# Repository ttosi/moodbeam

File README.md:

# moodbeam
Arduino, ESP8266 ESP-01 and NeoPixel light bar. Uses a pair of neopixels mounted on each end of an acrylic rod to create a beam of color. ~~The lights are controlled by a RESTful'ish API.~~

The original idea came from the fact that I needed a way to alert people when I was coding "in the zone" so I would, hopefully, be left alone. My plan was to just mount a couple of LEDs behind my LCD that would illuminate the wall red with a button click. The LEDs weren't bright enough to see during the day. Shining them through an acrylic rod with scores in it made the light more visible in bright conditions. The project grew into using different colors to indicate various moods I was in. Buttons became cumbersome so I added an ESP8266 and a mobile app that allows me to choose any color.

## Overall Architecture

### Moodbeam Controller
__Initial Configuration for moodbeam controller__ (`config.lua` does not exist on the ESP8266's flash):
* Configures itself in AP mode
* User connects to the MOODBEAM AP and browses to 192.168.4.1
* The ESP module returns a webpage where an SSID and password of the home network are entered (also an email and password that is used by the external node server)
* ESP module writes the information to `config.lua` and resets itself
* User recconects to their home network
   
__Normal Operation for moodbeam controller__ (`config.lua` exists on the ESP8266's flash):
* Reads the ssid, ssid password, username & password from `config.lua`
* Sets itself in station mode and connects to the home wifi network
* Makes a TCP connection to the external nodejs server sending the configured username and password which is registered on the server
* Sends a heartbeat byte to the server every hour(?) to keep the connection alive
   
### Server
__Initial User Setup__ 
* _Before_ a user configures a moodbeam they must have created an account
* User creates account: email address & password
* Confirm email account
* Send email which contains instructions and a link to the AP (so they don't have to type in an IP address)
* Configures as described above

__Normal User Opertation__
* A phonegap app or a web ui can be used to control the moodbeam from anywhere (WIP)

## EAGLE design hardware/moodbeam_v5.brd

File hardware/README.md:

### Schematics, parts and assembly.

#### Parts list
* Ardunion Nano ATMega328 5v
* ESP8266 ESP-01 Serial Wifi Wireless Transceiver
* 4 Channel Bi-Directional Logic Level Converter
* Pololu Step-Down Voltage Regulator D15V35F5S3
* 0.1" 2x4 crimp connector housing
* Some female crimp pins
* ~2 feet of 3/4 acrylic rod

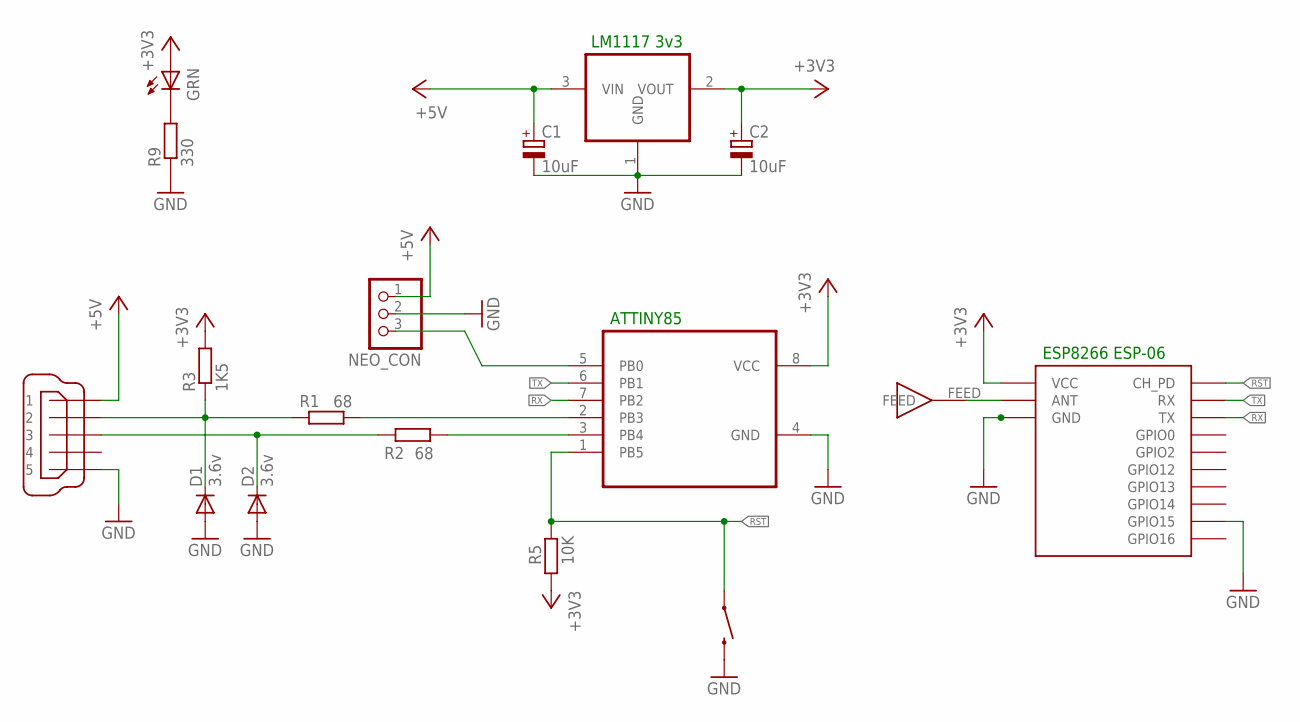
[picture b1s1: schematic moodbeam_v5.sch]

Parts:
C1, C2: 10uF; R/2012-12R
D1, D2: 3.6v; DO-214AC
IC1: REG1117; SOT223; MPN LM1117 3v3
JP1: NEO_CON; 1X03
LED1: GRN; CHIP-LED0805
R1, R2: 68; R0805
R3: 1K5; R0805
R5: 10K; R0805
R9: 330; R0805
S1: SWITCH-MOMENTARY-2SMD-1101NE; TACTILE-SWITCH-1101NE
U1: ATTINY85-20SU; SOIC127P798X216-8N
U$1: ESP06
U$2: ANT; ANTENNA-CERAMIC
X1: MINI-USB-32005-201; 32005-201

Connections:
+3V3: C2.+, IC1.2 (VOUT), LED1.A, R3.2, R5.1, U1.8 (VCC), U$1.VCC
+5V: C1.+, IC1.3 (VIN), JP1.1, X1.1
GND: C1.-, C2.-, D1.A, D2.A, IC1.1 (GND), JP1.2, R9.1, S1.2, U1.4 (GND), U$1.GND, U$1.GND1 (GND2), U$1.GND2 (GND3), U$1.GND3 (GND4), U$1.GND4 (GND5), U$1.GND5 (GND6), U$1.GND6 (GND7), U$1.GND7 (GND8), U$1.GPIO15, X1.5
unnamed: D1.C, R1.2, R3.1, X1.2
unnamed: R1.1, U1.2 (PB3)
unnamed: D2.C, R2.2, X1.3
unnamed: R2.1, U1.3 (PB4)
unnamed: U$1.ANT, U$2.FEED
unnamed: JP1.3, U1.5 (PB0)
unnamed: LED1.C, R9.2
RST: R5.2, S1.1, U1.1 (PB5), U$1.CH_PD
RX: U1.7 (PB2), U$1.TX
TX: U1.6 (PB1), U$1.RX

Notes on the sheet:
ATTINY85
LM1117 3v3
ESP8266 ESP-06

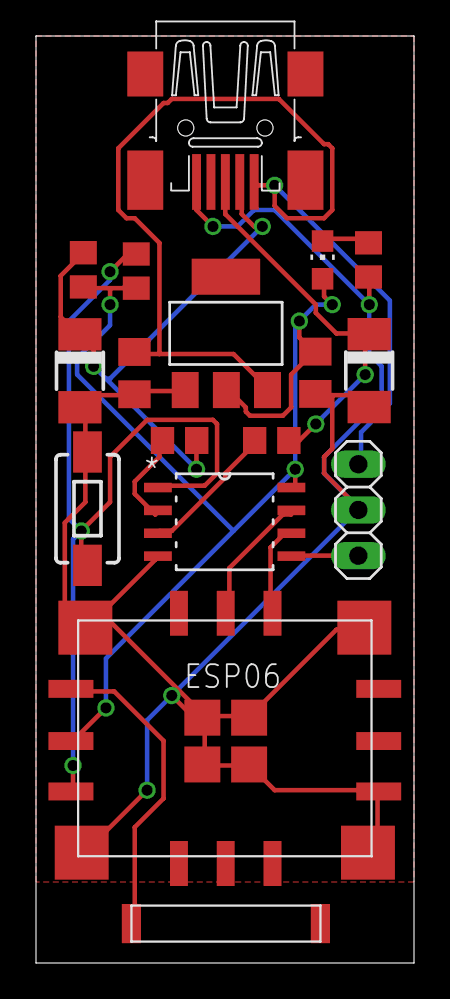
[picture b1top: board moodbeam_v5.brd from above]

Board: 2 copper layers, 21.0 x 51.5 mm, 17 parts (0 on the bottom side), 13 nets.

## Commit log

2015-02-18 Added init.lua
2015-02-18 Removing unused directories
2015-02-18 Updated folder structure
2015-02-18 Update phonegap files
2015-02-18 fixed .gitignore
2015-02-18 Fixing gitignore mistake
2015-02-18 Added arduino code
2015-02-18 Updating .gitignore
2015-02-18 Adding models
2015-02-18 Removed console print debugging
2015-02-19 Add schematics
2015-02-19 Move schematics to hardware folder
2015-02-19 Fixing deleted files
2015-02-19 Fixing again
2015-02-19 Removing TinyCad autosave file
2015-02-19 Updated schematic png
2015-02-20 Initial web UI
2015-02-20 Added better HTTP response headers
2015-02-20 Remove moodbeams-mobile
2015-02-20 Add phonegap skeleton
2015-02-21 Updating web
2015-02-21 Remove old .js
2015-02-21 Remove old .css
2015-03-06 Refreshing
2015-03-06 Rewrite ESP8266 module to add ap and station modes
2015-03-06 Add server
2015-03-06 Add images
2015-03-08 Change moodbeams -> moodbeam
2015-03-08 Rename moodbeams-schematic.dsn to moodbeam-schematic.dsn
2015-03-08 Remove get/set presetsfrom EEPROM
2015-03-08 Use nodejs express
2015-03-08 Remove node_modules
2015-03-09 Use JSON for client to server commands
2015-03-09 Update packages
2015-03-09 Implement new server protocol
2015-03-09 Update web client
2015-03-10 Updated URL
2015-03-10 Remove old JS
2015-03-10 Set proper URL
2015-03-12 Updated protocol
2015-03-12 Update arduino protocol
2015-03-13 Add fade & alternate colors effects
2015-03-13 Add hardware images
2015-03-13 Small fix ups
2015-03-13 Fix ups
2015-03-15 Stable arduino code
2015-04-25 updated server
2015-05-13 Add v5 esp code
2015-05-13 Add updated schematic and board
2015-05-13 Reduce complexity of esp module
2015-05-14 Add commands to attiny
2015-05-14 web and server updated commands
2015-05-14 correct uC files
2016-05-10 remove -omap option from picocom command
2016-09-04 not sure

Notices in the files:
parts and their libraries:
SparkFun-Electromechanical: Licensing: Creative Commons ShareAlike 4.0 International - https://creativecommons.org/licenses/by-sa/4.0
